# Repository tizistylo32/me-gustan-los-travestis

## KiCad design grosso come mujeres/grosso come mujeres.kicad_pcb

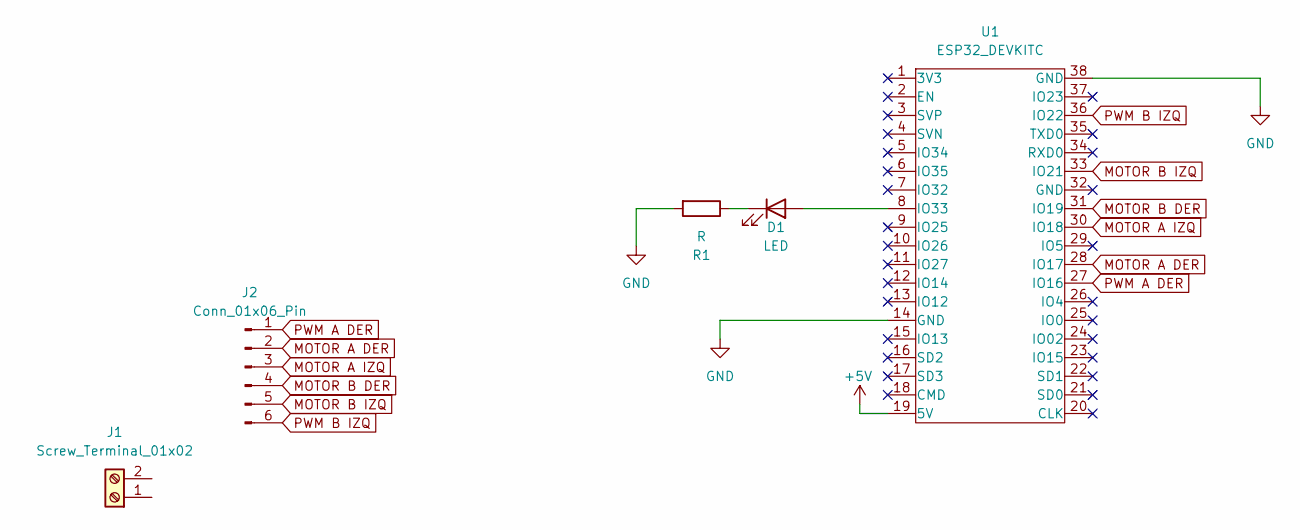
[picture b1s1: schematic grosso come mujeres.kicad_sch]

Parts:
D1: LED
J1: Screw_Terminal_01x02; BORNERA2_AZUL
J2: Conn_01x06_Pin
R1: R; R_Axial_DIN0204_L3.6mm_D1.6mm_P5.08mm_Horizontal
U1: ESP32_DEVKITC

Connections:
+5V: U1.19 (5V)
GND: R1.2, U1.14 (GND), U1.38 (GND)
MOTOR A DER: J2.2, U1.28 (IO17)
MOTOR A IZQ: J2.3, U1.30 (IO18)
MOTOR B DER: J2.4, U1.31 (IO19)
MOTOR B IZQ: J2.5, U1.33 (IO21)
unnamed: D1.2 (A), U1.8 (IO33)
unnamed: D1.1 (K), R1.1
PWM A DER: J2.1, U1.27 (IO16)
PWM B IZQ: J2.6, U1.36 (IO22)

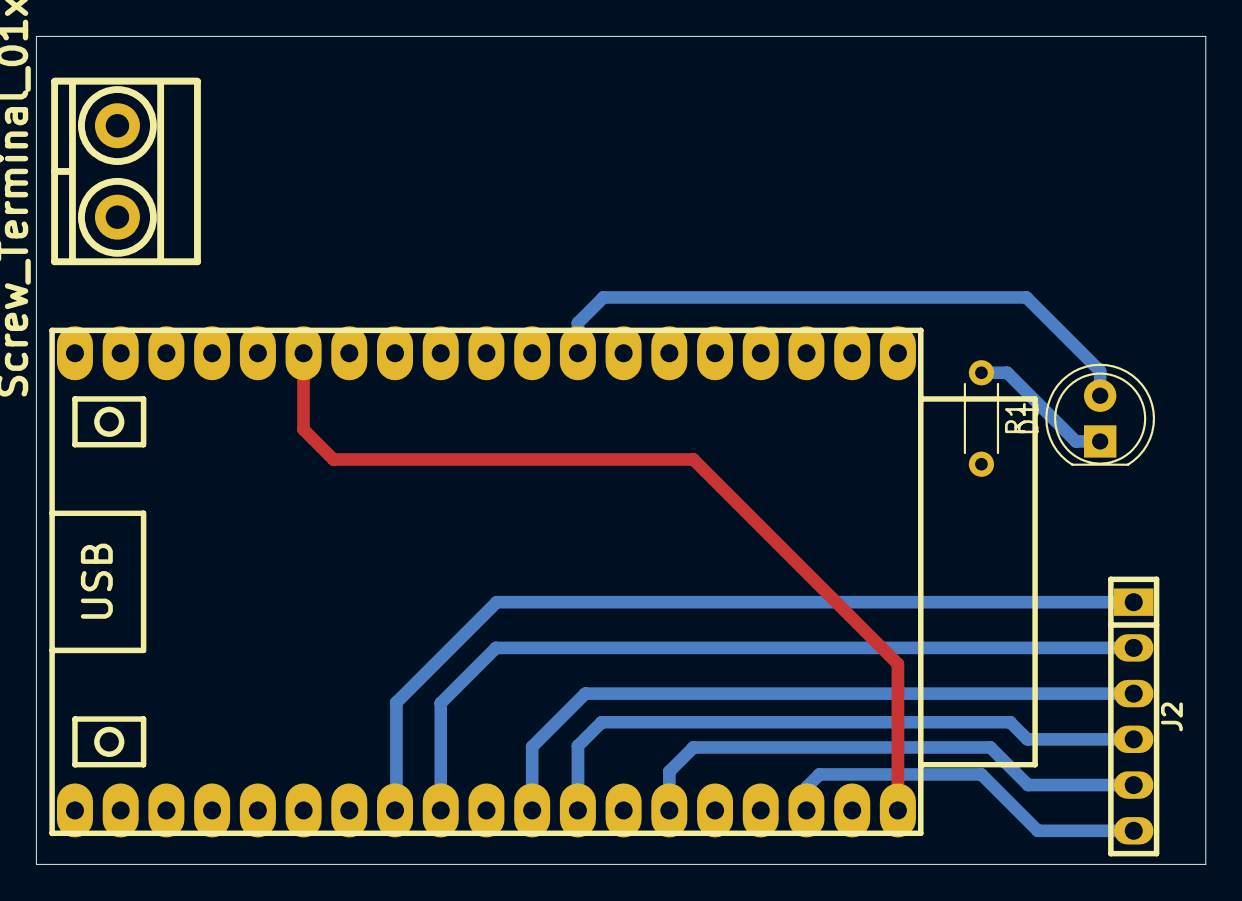
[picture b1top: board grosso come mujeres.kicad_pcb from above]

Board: 2 copper layers, 65.0 x 46.0 mm, 5 parts (0 on the bottom side), 9 nets.

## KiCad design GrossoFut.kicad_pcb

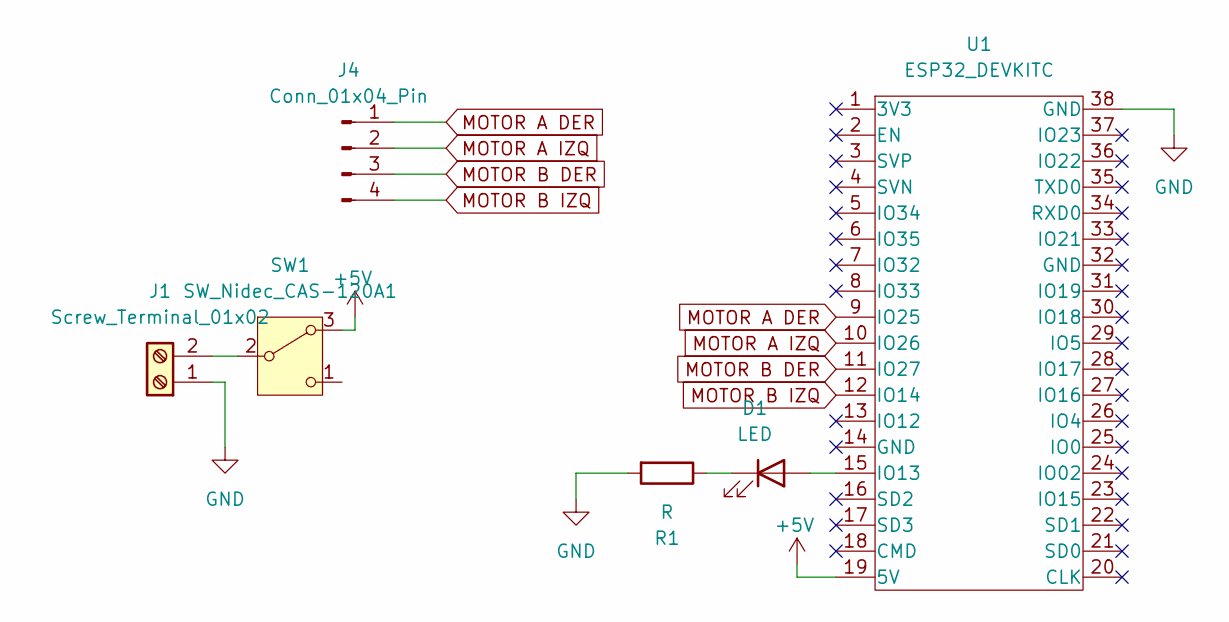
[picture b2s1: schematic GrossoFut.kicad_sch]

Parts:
D1: LED
J1: Screw_Terminal_01x02; BORNERA2_AZUL
J4: Conn_01x04_Pin; pin_strip_4
R1: R; R_Axial_DIN0204_L3.6mm_D1.6mm_P5.08mm_Horizontal
SW1: SW_Nidec_CAS-120A1; Nidec_Copal_CAS-120A
U1: ESP32_DEVKITC

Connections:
+5V: SW1.3 (A), U1.19 (5V)
GND: J1.1, R1.2, U1.38 (GND)
MOTOR A DER: J4.1, U1.9 (IO25)
MOTOR A IZQ: J4.2, U1.10 (IO26)
MOTOR B DER: J4.3, U1.11 (IO27)
MOTOR B IZQ: J4.4, U1.12 (IO14)
unnamed: D1.2 (A), U1.15 (IO13)
unnamed: D1.1 (K), R1.1
unnamed: J1.2, SW1.2 (B)

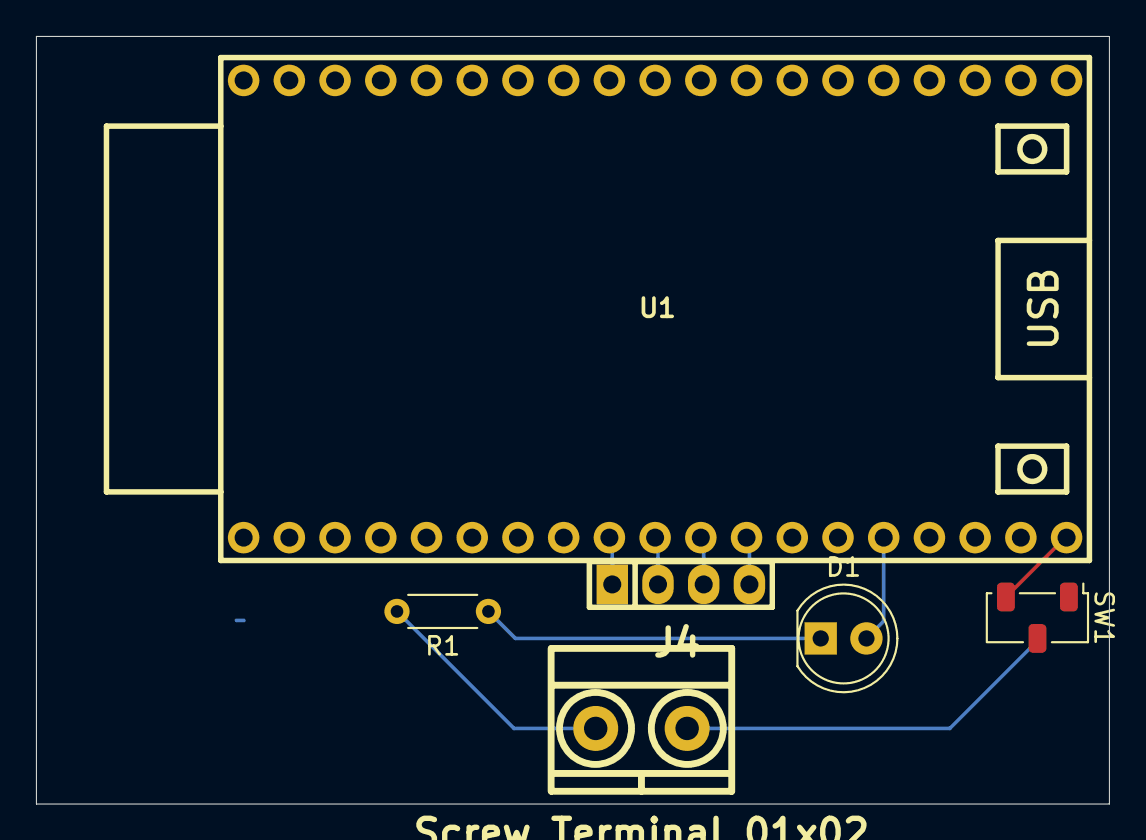
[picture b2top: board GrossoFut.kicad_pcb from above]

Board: 2 copper layers, 59.6 x 42.6 mm, 6 parts (0 on the bottom side), 9 nets.
